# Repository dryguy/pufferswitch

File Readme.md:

## pufferswitch

pufferswitch is a PCB design for a switchable capacitor. A 10-position switch is used to select one of 10 available capacitors on the PCB. This project was inspired by a similar [rotary potentiometer switch](https://github.com/sparkfun/Rotary_Switch_Potentiometer) from Sparkfun.

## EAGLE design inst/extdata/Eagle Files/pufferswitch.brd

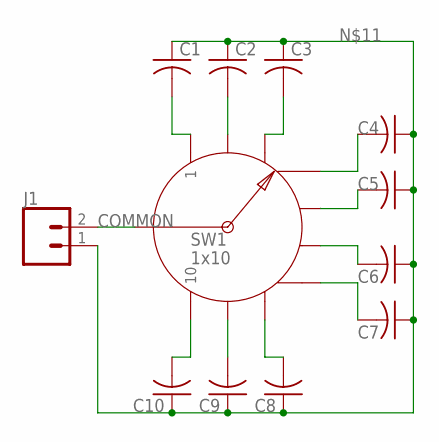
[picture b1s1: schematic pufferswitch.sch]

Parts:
C1, C2, C3, C4, C5, C6, C7, C8, C9, C10: C-US025-024X044; C025-024X044
J1: CONN_02; 1X02
SW1: 1x10; ROTARY_SWITCH_1X10_KIT

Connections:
COMMON: J1.2, SW1.COMMON
unnamed: C1.2, SW1.1
unnamed: C2.2, SW1.2
unnamed: C3.2, SW1.3
unnamed: C4.2, SW1.4
unnamed: C5.2, SW1.5
unnamed: C6.2, SW1.6
unnamed: C7.2, SW1.7
unnamed: C8.2, SW1.8
unnamed: C9.2, SW1.9
unnamed: C10.2, SW1.10
unnamed: C1.1, C2.1, C3.1, C4.1, C5.1, C6.1, C7.1, C8.1, C9.1, C10.1, J1.1

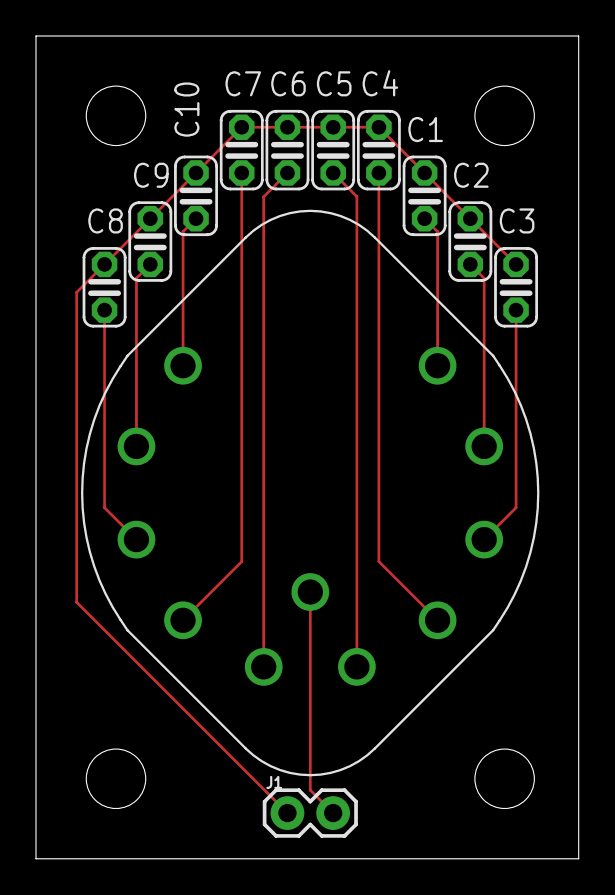
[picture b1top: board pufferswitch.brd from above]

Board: 2 copper layers, 30.2 x 45.7 mm, 16 parts (0 on the bottom side), 12 nets.

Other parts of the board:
STANDOFF1, STANDOFF2, STANDOFF3, STANDOFF4: STAND-OFF

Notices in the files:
parts and their libraries:
SparkFun-Connectors: Licensing: Creative Commons ShareAlike 4.0 International - https://creativecommons.org/licenses/by-sa/4.0
